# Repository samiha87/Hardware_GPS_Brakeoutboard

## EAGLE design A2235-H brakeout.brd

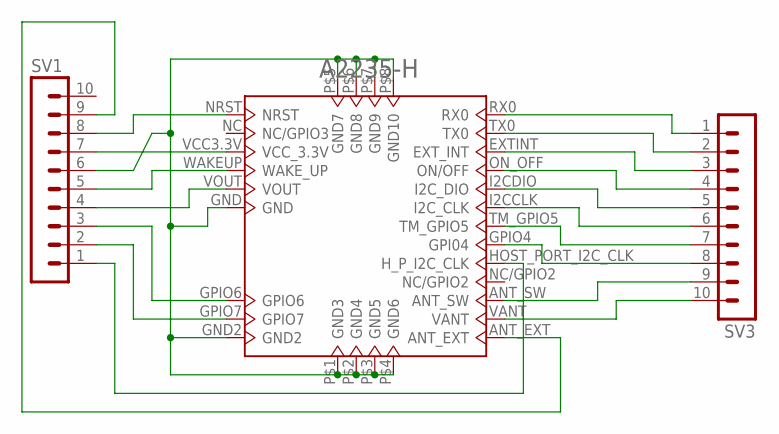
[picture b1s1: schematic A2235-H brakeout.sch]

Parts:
SV1, SV3: MA10-1
U$1: A2235-H; A2235MAESTRO

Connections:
GND: SV1.6, U$1.GND, U$1.GND2, U$1.P$1 (GND3), U$1.P$2 (GND4), U$1.P$3 (GND5), U$1.P$4 (GND6), U$1.P$5 (GND7), U$1.P$6 (GND8), U$1.P$7 (GND9), U$1.P$8 (GND10)
unnamed: SV3.9, U$1.ANT_SW
unnamed: SV1.8, U$1.NRST
unnamed: SV3.10, U$1.VANT
unnamed: SV1.5, U$1.WAKEUP (WAKE_UP)
unnamed: SV1.4, U$1.VOUT
unnamed: SV1.3, U$1.GPIO6
unnamed: SV1.2, U$1.GPIO7
unnamed: SV1.1, U$1.HOST_PORT_I2C_CLK (H_P_I2C_CLK)
unnamed: SV3.1, U$1.RX0
unnamed: SV3.2, U$1.TX0
unnamed: SV3.3, U$1.EXTINT (EXT_INT)
unnamed: SV3.4, U$1.ON_OFF (ON/OFF)
unnamed: SV3.5, U$1.I2CDIO (I2C_DIO)
unnamed: SV3.6, U$1.I2CCLK (I2C_CLK)
unnamed: SV3.7, U$1.TM_GPIO5
unnamed: SV3.8, U$1.GPIO4 (GPI04)
unnamed: SV1.9, U$1.ANT_EXT
VCC: SV1.7, U$1.VCC3.3V (VCC_3.3V)

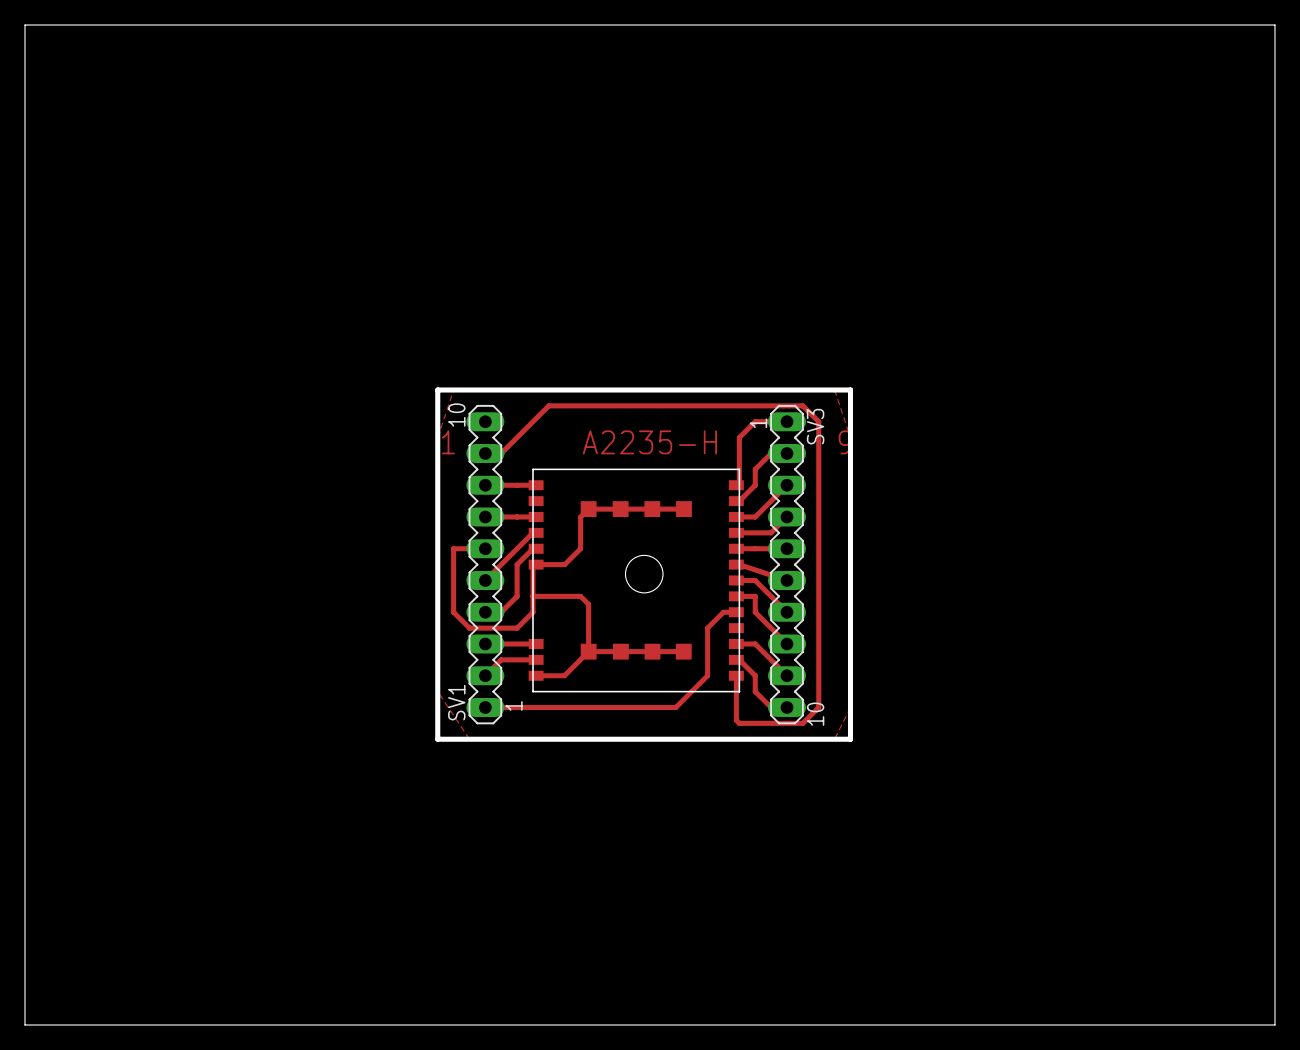
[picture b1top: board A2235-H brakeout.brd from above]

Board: 2 copper layers, 100.0 x 80.0 mm, 3 parts (0 on the bottom side), 19 nets.

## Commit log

2019-08-24 A2235-H Brakeout board
